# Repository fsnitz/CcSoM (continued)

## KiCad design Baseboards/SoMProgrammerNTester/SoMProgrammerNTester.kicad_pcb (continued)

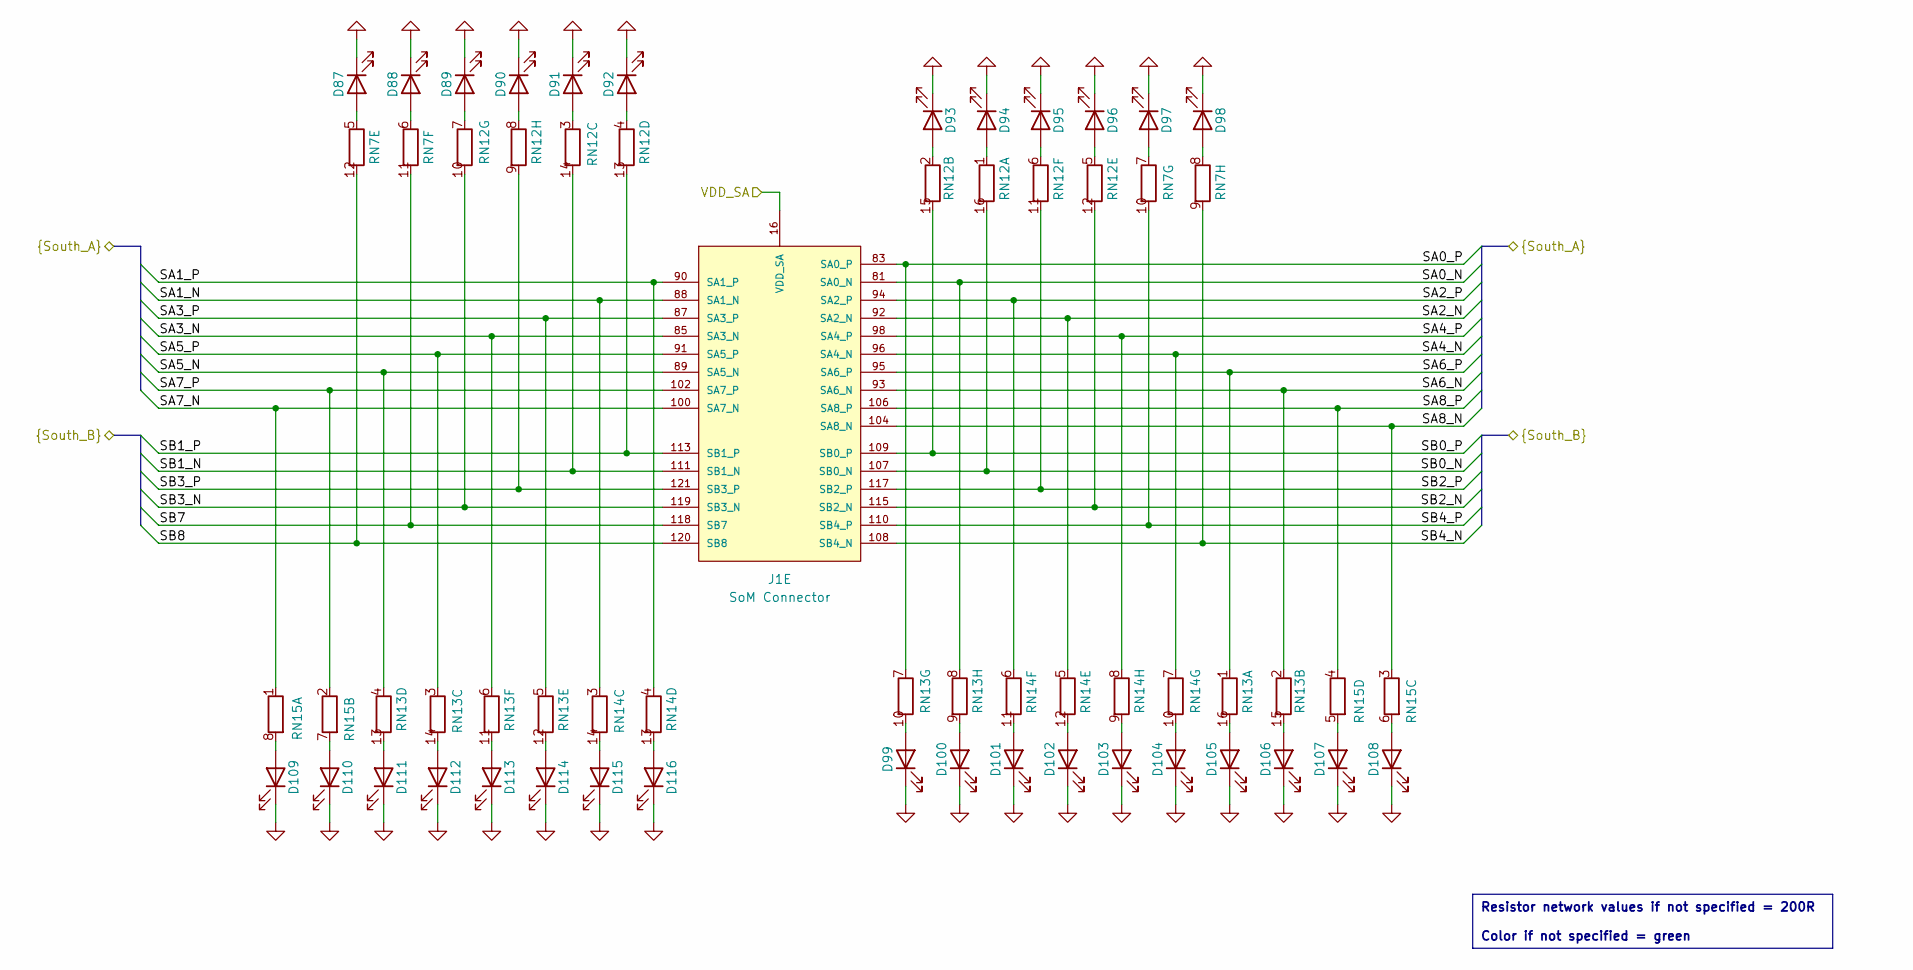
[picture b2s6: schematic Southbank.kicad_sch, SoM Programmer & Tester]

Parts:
D87, D88, D89, D90, D91, D92, D93, D94, D95, D96, D97, D98, D99, D100, D101, D102, D103, D104, D105, D106, D107, D108, D109, D110, D111, D112, D113, D114, D115, D116: Green; LED_0603_1608Metric; Mouser Part Number 710-150060VS75000
J1: SoM Connector; SoM_Connector; Mouser Part Number 571-1473005-1
RN7, RN12, RN13, RN14: 200R; R_Array_Convex_8x0602; Mouser Part Number 667-EXB-2HV201JV
RN15: 200R; R_Array_Convex_4x0603; Mouser Part Number 667-EXB-38V201JV

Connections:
/Header Interface/SA0_N: J1.81 (SA0_N), RN13.8 (R8.1); also elsewhere on the board
/Header Interface/SA0_P: J1.83 (SA0_P), RN13.7 (R7.1); also elsewhere on the board
/Header Interface/SA1_N: J1.88 (SA1_N), RN14.3 (R3.1); also elsewhere on the board
/Header Interface/SA1_P: J1.90 (SA1_P), RN14.4 (R4.1); also elsewhere on the board
/Header Interface/SA2_N: J1.92 (SA2_N), RN14.5 (R5.1); also elsewhere on the board
/Header Interface/SA2_P: J1.94 (SA2_P), RN14.6 (R6.1); also elsewhere on the board
/Header Interface/SA3_N: J1.85 (SA3_N), RN13.6 (R6.1); also elsewhere on the board
/Header Interface/SA3_P: J1.87 (SA3_P), RN13.5 (R5.1); also elsewhere on the board
/Header Interface/SA4_N: J1.96 (SA4_N), RN14.7 (R7.1); also elsewhere on the board
/Header Interface/SA4_P: J1.98 (SA4_P), RN14.8 (R8.1); also elsewhere on the board
/Header Interface/SA5_N: J1.89 (SA5_N), RN13.4 (R4.1); also elsewhere on the board
/Header Interface/SA5_P: J1.91 (SA5_P), RN13.3 (R3.1); also elsewhere on the board
/Header Interface/SA6_N: J1.93 (SA6_N), RN13.2 (R2.1); also elsewhere on the board
/Header Interface/SA6_P: J1.95 (SA6_P), RN13.1 (R1.1); also elsewhere on the board
/Header Interface/SA7_N: J1.100 (SA7_N), RN15.1 (R1.1); also elsewhere on the board
/Header Interface/SA7_P: J1.102 (SA7_P), RN15.2 (R2.1); also elsewhere on the board
/Header Interface/SA8_N: J1.104 (SA8_N), RN15.3 (R3.1); also elsewhere on the board
/Header Interface/SA8_P: J1.106 (SA8_P), RN15.4 (R4.1); also elsewhere on the board
/Header Interface/SB0_N: J1.107 (SB0_N), RN12.16 (R1.2); also elsewhere on the board
/Header Interface/SB0_P: J1.109 (SB0_P), RN12.15 (R2.2); also elsewhere on the board
/Header Interface/SB1_N: J1.111 (SB1_N), RN12.14 (R3.2); also elsewhere on the board
/Header Interface/SB1_P: J1.113 (SB1_P), RN12.13 (R4.2); also elsewhere on the board
/Header Interface/SB2_N: J1.115 (SB2_N), RN12.12 (R5.2); also elsewhere on the board
/Header Interface/SB2_P: J1.117 (SB2_P), RN12.11 (R6.2); also elsewhere on the board
/Header Interface/SB3_N: J1.119 (SB3_N), RN12.10 (R7.2); also elsewhere on the board
/Header Interface/SB3_P: J1.121 (SB3_P), RN12.9 (R8.2); also elsewhere on the board
/Header Interface/SB4_N: J1.108 (SB4_N), RN7.9 (R8.2); also elsewhere on the board
/Header Interface/SB4_P: J1.110 (SB4_P), RN7.10 (R7.2); also elsewhere on the board
/Header Interface/SB7: J1.118 (SB7), RN7.11 (R6.2); also elsewhere on the board
/Header Interface/SB8: J1.120 (SB8), RN7.12 (R5.2); also elsewhere on the board
/Header Interface/Southbank/VDD_SA: J1.16 (VDD_SA); also elsewhere on the board
GND: D87.1 (K), D88.1 (K), D89.1 (K), D90.1 (K), D91.1 (K), D92.1 (K), D93.1 (K), D94.1 (K), D95.1 (K), D96.1 (K), D97.1 (K), D98.1 (K), D99.1 (K), D100.1 (K), D101.1 (K), D102.1 (K), D103.1 (K), D104.1 (K), D105.1 (K), D106.1 (K), D107.1 (K), D108.1 (K), D109.1 (K), D110.1 (K), D111.1 (K), D112.1 (K), D113.1 (K), D114.1 (K), D115.1 (K), D116.1 (K); also elsewhere on the board
unnamed: D87.2 (A), RN7.5 (R5.1)
unnamed: D88.2 (A), RN7.6 (R6.1)
unnamed: D89.2 (A), RN12.7 (R7.1)
unnamed: D90.2 (A), RN12.8 (R8.1)
unnamed: D91.2 (A), RN12.3 (R3.1)
unnamed: D92.2 (A), RN12.4 (R4.1)
unnamed: D93.2 (A), RN12.2 (R2.1)
unnamed: D94.2 (A), RN12.1 (R1.1)
unnamed: D95.2 (A), RN12.6 (R6.1)
unnamed: D96.2 (A), RN12.5 (R5.1)
unnamed: D97.2 (A), RN7.7 (R7.1)
unnamed: D98.2 (A), RN7.8 (R8.1)
unnamed: D99.2 (A), RN13.10 (R7.2)
unnamed: D100.2 (A), RN13.9 (R8.2)
unnamed: D101.2 (A), RN14.11 (R6.2)
unnamed: D102.2 (A), RN14.12 (R5.2)
unnamed: D103.2 (A), RN14.9 (R8.2)
unnamed: D104.2 (A), RN14.10 (R7.2)
unnamed: D105.2 (A), RN13.16 (R1.2)
unnamed: D106.2 (A), RN13.15 (R2.2)
unnamed: D107.2 (A), RN15.5 (R4.2)
unnamed: D108.2 (A), RN15.6 (R3.2)
unnamed: D109.2 (A), RN15.8 (R1.2)
unnamed: D110.2 (A), RN15.7 (R2.2)
unnamed: D111.2 (A), RN13.13 (R4.2)
unnamed: D112.2 (A), RN13.14 (R3.2)
unnamed: D113.2 (A), RN13.11 (R6.2)
unnamed: D114.2 (A), RN13.12 (R5.2)
unnamed: D115.2 (A), RN14.14 (R3.2)
unnamed: D116.2 (A), RN14.13 (R4.2)

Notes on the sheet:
Resistor network values if not specified = 200R Color if not specified = green

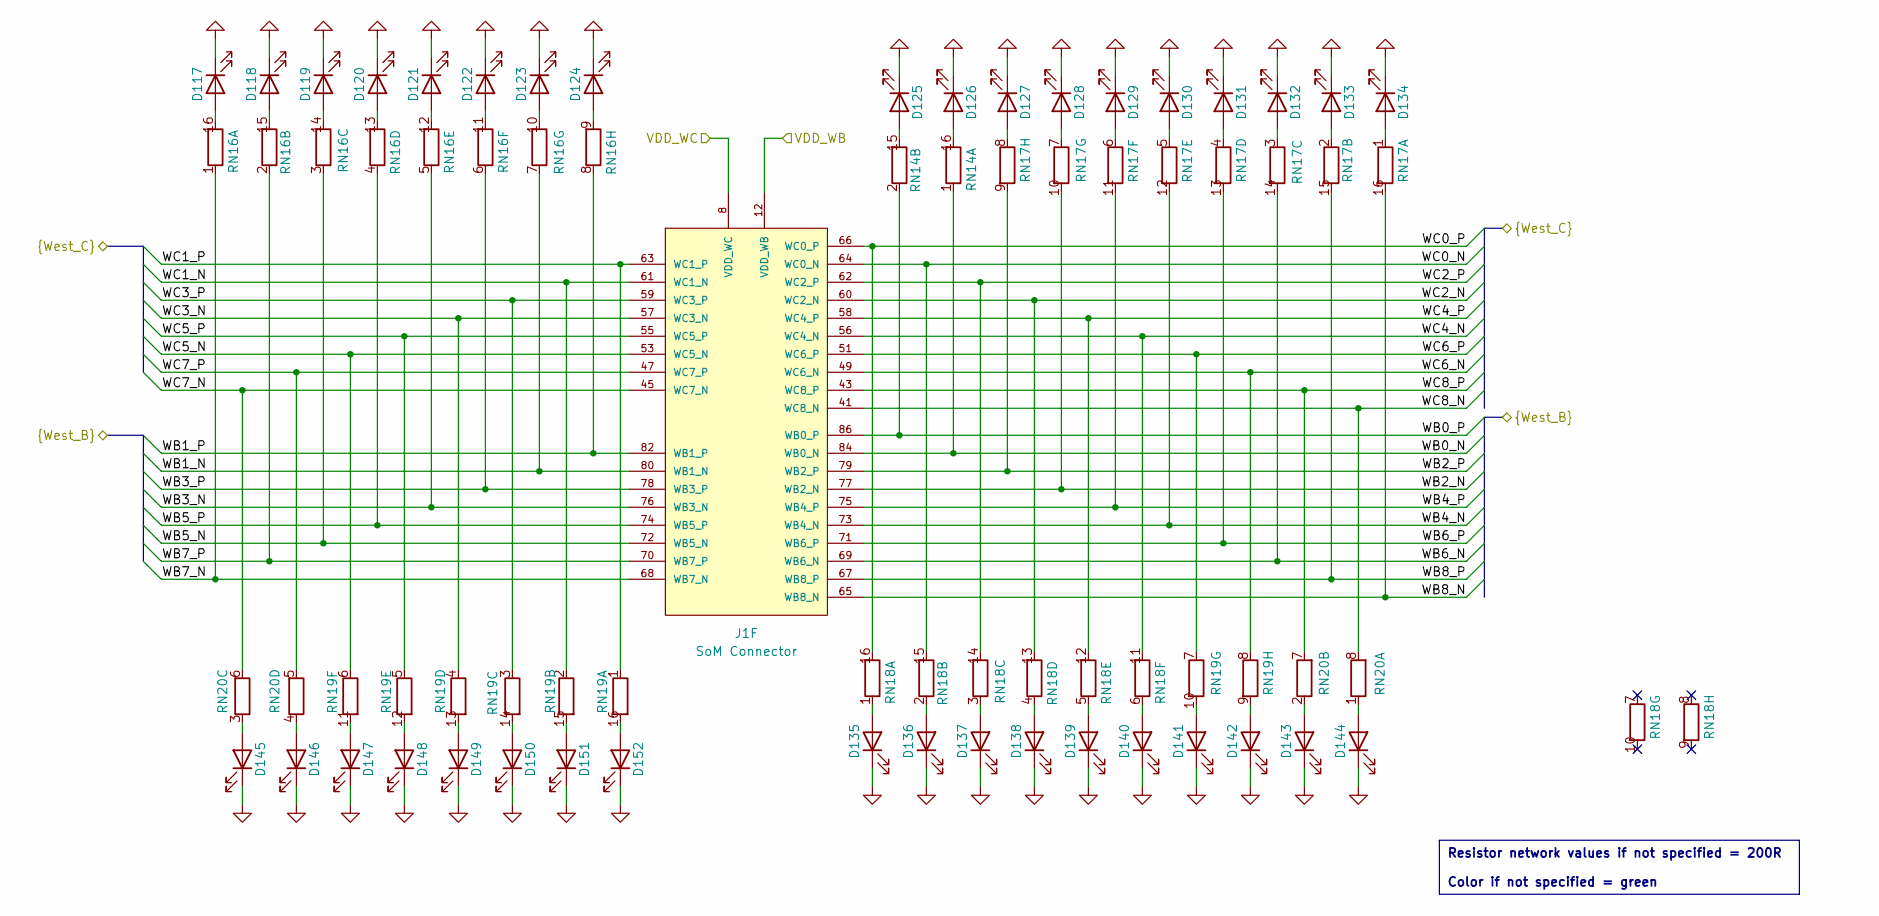
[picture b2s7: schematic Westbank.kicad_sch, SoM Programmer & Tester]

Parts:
D117, D118, D119, D120, D121, D122, D123, D124, D125, D126, D127, D128, D129, D130, D131, D132, D133, D134, D135, D136, D137, D138, D139, D140, D141, D142, D143, D144, D145, D146, D147, D148, D149, D150, D151, D152: Green; LED_0603_1608Metric; Mouser Part Number 710-150060VS75000
J1: SoM Connector; SoM_Connector; Mouser Part Number 571-1473005-1
RN14, RN16, RN17, RN18, RN19: 200R; R_Array_Convex_8x0602; Mouser Part Number 667-EXB-2HV201JV
RN20: 200R; R_Array_Convex_4x0603; Mouser Part Number 667-EXB-38V201JV

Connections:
/Header Interface/WB0_N: J1.84 (WB0_N), RN14.1 (R1.1); also elsewhere on the board
/Header Interface/WB0_P: J1.86 (WB0_P), RN14.2 (R2.1); also elsewhere on the board
/Header Interface/WB1_N: J1.80 (WB1_N), RN16.7 (R7.1); also elsewhere on the board
/Header Interface/WB1_P: J1.82 (WB1_P), RN16.8 (R8.1); also elsewhere on the board
/Header Interface/WB2_N: J1.77 (WB2_N), RN17.10 (R7.2); also elsewhere on the board
/Header Interface/WB2_P: J1.79 (WB2_P), RN17.9 (R8.2); also elsewhere on the board
/Header Interface/WB3_N: J1.76 (WB3_N), RN16.5 (R5.1); also elsewhere on the board
/Header Interface/WB3_P: J1.78 (WB3_P), RN16.6 (R6.1); also elsewhere on the board
/Header Interface/WB4_N: J1.73 (WB4_N), RN17.12 (R5.2); also elsewhere on the board
/Header Interface/WB4_P: J1.75 (WB4_P), RN17.11 (R6.2); also elsewhere on the board
/Header Interface/WB5_N: J1.72 (WB5_N), RN16.3 (R3.1); also elsewhere on the board
/Header Interface/WB5_P: J1.74 (WB5_P), RN16.4 (R4.1); also elsewhere on the board
/Header Interface/WB6_N: J1.69 (WB6_N), RN17.14 (R3.2); also elsewhere on the board
/Header Interface/WB6_P: J1.71 (WB6_P), RN17.13 (R4.2); also elsewhere on the board
/Header Interface/WB7_N: J1.68 (WB7_N), RN16.1 (R1.1); also elsewhere on the board
/Header Interface/WB7_P: J1.70 (WB7_P), RN16.2 (R2.1); also elsewhere on the board
/Header Interface/WB8_N: J1.65 (WB8_N), RN17.16 (R1.2); also elsewhere on the board
/Header Interface/WB8_P: J1.67 (WB8_P), RN17.15 (R2.2); also elsewhere on the board
/Header Interface/WC0_N: J1.64 (WC0_N), RN18.15 (R2.2); also elsewhere on the board
/Header Interface/WC0_P: J1.66 (WC0_P), RN18.16 (R1.2); also elsewhere on the board
/Header Interface/WC1_N: J1.61 (WC1_N), RN19.2 (R2.1); also elsewhere on the board
/Header Interface/WC1_P: J1.63 (WC1_P), RN19.1 (R1.1); also elsewhere on the board
/Header Interface/WC2_N: J1.60 (WC2_N), RN18.13 (R4.2); also elsewhere on the board
/Header Interface/WC2_P: J1.62 (WC2_P), RN18.14 (R3.2); also elsewhere on the board
/Header Interface/WC3_N: J1.57 (WC3_N), RN19.4 (R4.1); also elsewhere on the board
/Header Interface/WC3_P: J1.59 (WC3_P), RN19.3 (R3.1); also elsewhere on the board
/Header Interface/WC4_N: J1.56 (WC4_N), RN18.11 (R6.2); also elsewhere on the board
/Header Interface/WC4_P: J1.58 (WC4_P), RN18.12 (R5.2); also elsewhere on the board
/Header Interface/WC5_N: J1.53 (WC5_N), RN19.6 (R6.1); also elsewhere on the board
/Header Interface/WC5_P: J1.55 (WC5_P), RN19.5 (R5.1); also elsewhere on the board
/Header Interface/WC6_N: J1.49 (WC6_N), RN19.8 (R8.1); also elsewhere on the board
/Header Interface/WC6_P: J1.51 (WC6_P), RN19.7 (R7.1); also elsewhere on the board
/Header Interface/WC7_N: J1.45 (WC7_N), RN20.6 (R3.2); also elsewhere on the board
/Header Interface/WC7_P: J1.47 (WC7_P), RN20.5 (R4.2); also elsewhere on the board
/Header Interface/WC8_N: J1.41 (WC8_N), RN20.8 (R1.2); also elsewhere on the board
/Header Interface/WC8_P: J1.43 (WC8_P), RN20.7 (R2.2); also elsewhere on the board
/Header Interface/Westbank/VDD_WB: J1.12 (VDD_WB); also elsewhere on the board
/Header Interface/Westbank/VDD_WC: J1.8 (VDD_WC); also elsewhere on the board
GND: D117.1 (K), D118.1 (K), D119.1 (K), D120.1 (K), D121.1 (K), D122.1 (K), D123.1 (K), D124.1 (K), D125.1 (K), D126.1 (K), D127.1 (K), D128.1 (K), D129.1 (K), D130.1 (K), D131.1 (K), D132.1 (K), D133.1 (K), D134.1 (K), D135.1 (K), D136.1 (K), D137.1 (K), D138.1 (K), D139.1 (K), D140.1 (K), D141.1 (K), D142.1 (K), D143.1 (K), D144.1 (K), D145.1 (K), D146.1 (K), D147.1 (K), D148.1 (K), D149.1 (K), D150.1 (K), D151.1 (K), D152.1 (K); also elsewhere on the board
unnamed: D117.2 (A), RN16.16 (R1.2)
unnamed: D118.2 (A), RN16.15 (R2.2)
unnamed: D119.2 (A), RN16.14 (R3.2)
unnamed: D120.2 (A), RN16.13 (R4.2)
unnamed: D121.2 (A), RN16.12 (R5.2)
unnamed: D122.2 (A), RN16.11 (R6.2)
unnamed: D123.2 (A), RN16.10 (R7.2)
unnamed: D124.2 (A), RN16.9 (R8.2)
unnamed: D125.2 (A), RN14.15 (R2.2)
unnamed: D126.2 (A), RN14.16 (R1.2)
unnamed: D127.2 (A), RN17.8 (R8.1)
unnamed: D128.2 (A), RN17.7 (R7.1)
unnamed: D129.2 (A), RN17.6 (R6.1)
unnamed: D130.2 (A), RN17.5 (R5.1)
unnamed: D131.2 (A), RN17.4 (R4.1)
unnamed: D132.2 (A), RN17.3 (R3.1)
unnamed: D133.2 (A), RN17.2 (R2.1)
unnamed: D134.2 (A), RN17.1 (R1.1)
unnamed: D135.2 (A), RN18.1 (R1.1)
unnamed: D136.2 (A), RN18.2 (R2.1)
unnamed: D137.2 (A), RN18.3 (R3.1)
unnamed: D138.2 (A), RN18.4 (R4.1)
unnamed: D139.2 (A), RN18.5 (R5.1)
unnamed: D140.2 (A), RN18.6 (R6.1)
unnamed: D141.2 (A), RN19.10 (R7.2)
unnamed: D142.2 (A), RN19.9 (R8.2)
unnamed: D143.2 (A), RN20.2 (R2.1)
unnamed: D144.2 (A), RN20.1 (R1.1)
unnamed: D145.2 (A), RN20.3 (R3.1)
unnamed: D146.2 (A), RN20.4 (R4.1)
unnamed: D147.2 (A), RN19.11 (R6.2)
unnamed: D148.2 (A), RN19.12 (R5.2)
unnamed: D149.2 (A), RN19.13 (R4.2)
unnamed: D150.2 (A), RN19.14 (R3.2)
unnamed: D151.2 (A), RN19.15 (R2.2)
unnamed: D152.2 (A), RN19.16 (R1.2)

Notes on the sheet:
Resistor network values if not specified = 200R Color if not specified = green

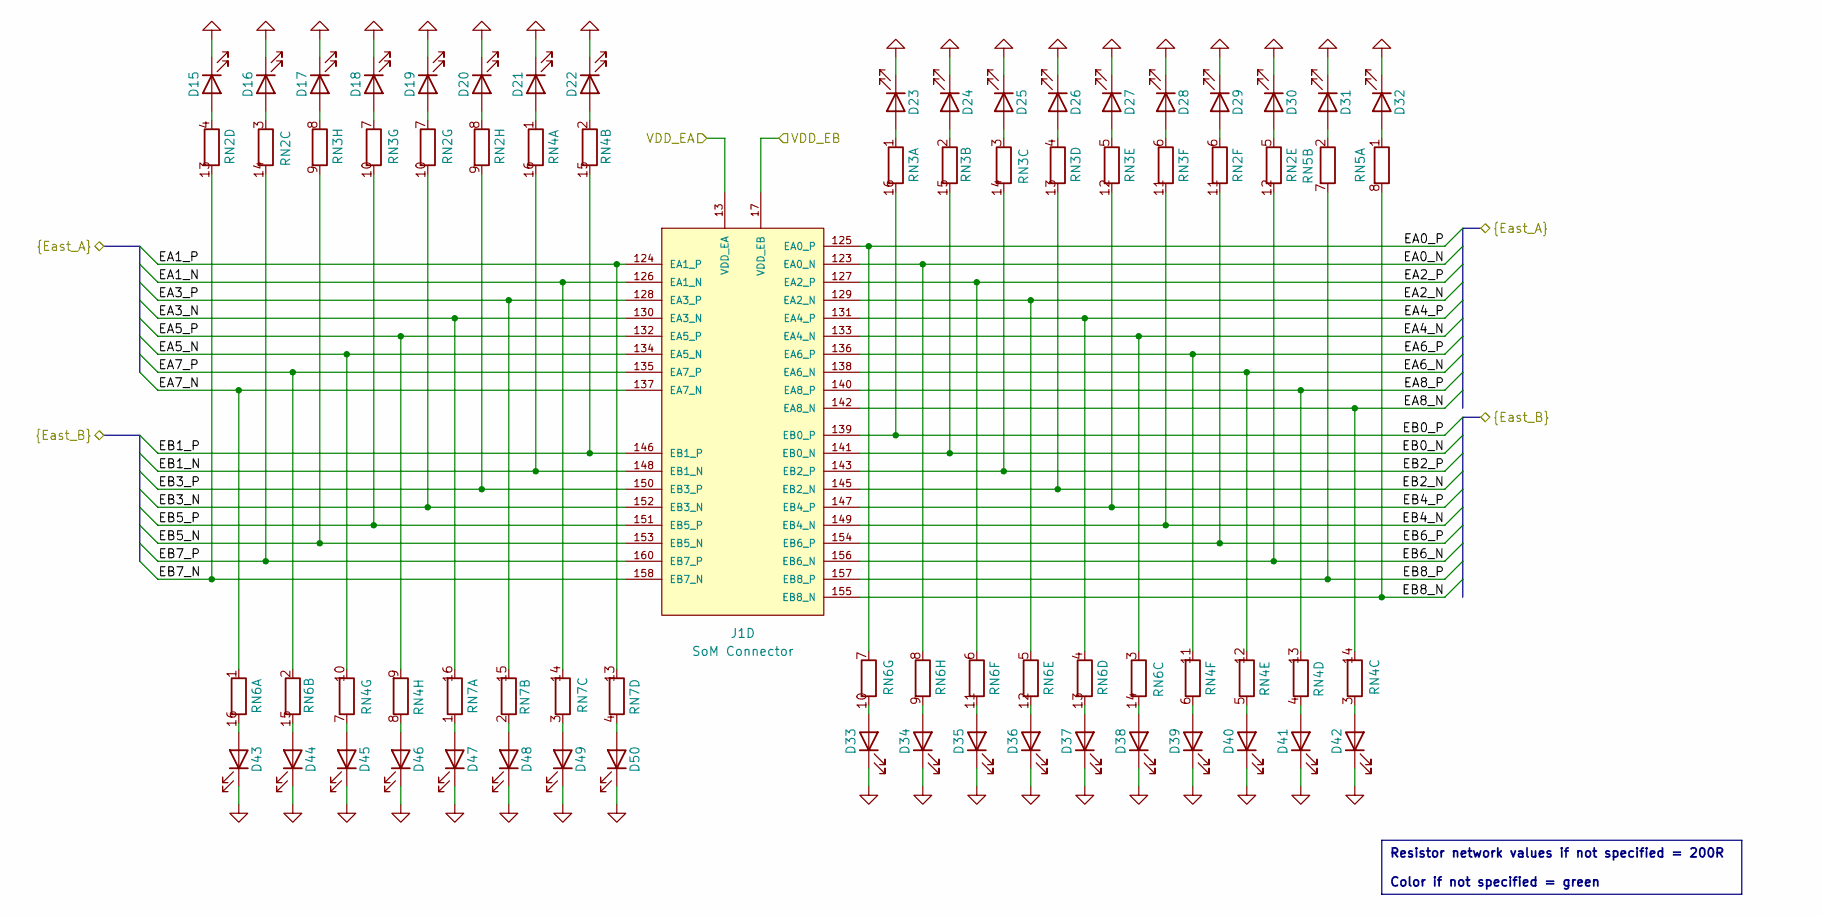
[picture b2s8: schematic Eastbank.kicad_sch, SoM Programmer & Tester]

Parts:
D15, D16, D17, D18, D19, D20, D21, D22, D23, D24, D25, D26, D27, D28, D29, D30, D31, D32, D33, D34, D35, D36, D37, D38, D39, D40, D41, D42, D43, D44, D45, D46, D47, D48, D49, D50: Green; LED_0603_1608Metric; Mouser Part Number 710-150060VS75000
J1: SoM Connector; SoM_Connector; Mouser Part Number 571-1473005-1
RN2, RN3, RN4, RN6, RN7: 200R; R_Array_Convex_8x0602; Mouser Part Number 667-EXB-2HV201JV
RN5: 200R; R_Array_Convex_4x0603; Mouser Part Number 667-EXB-38V201JV

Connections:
/Header Interface/EA0_N: J1.123 (EA0_N), RN6.8 (R8.1); also elsewhere on the board
/Header Interface/EA0_P: J1.125 (EA0_P), RN6.7 (R7.1); also elsewhere on the board
/Header Interface/EA1_N: J1.126 (EA1_N), RN7.14 (R3.2); also elsewhere on the board
/Header Interface/EA1_P: J1.124 (EA1_P), RN7.13 (R4.2); also elsewhere on the board
/Header Interface/EA2_N: J1.129 (EA2_N), RN6.5 (R5.1); also elsewhere on the board
/Header Interface/EA2_P: J1.127 (EA2_P), RN6.6 (R6.1); also elsewhere on the board
/Header Interface/EA3_N: J1.130 (EA3_N), RN7.16 (R1.2); also elsewhere on the board
/Header Interface/EA3_P: J1.128 (EA3_P), RN7.15 (R2.2); also elsewhere on the board
/Header Interface/EA4_N: J1.133 (EA4_N), RN6.3 (R3.1); also elsewhere on the board
/Header Interface/EA4_P: J1.131 (EA4_P), RN6.4 (R4.1); also elsewhere on the board
/Header Interface/EA5_N: J1.134 (EA5_N), RN4.10 (R7.2); also elsewhere on the board
/Header Interface/EA5_P: J1.132 (EA5_P), RN4.9 (R8.2); also elsewhere on the board
/Header Interface/EA6_N: J1.138 (EA6_N), RN4.12 (R5.2); also elsewhere on the board
/Header Interface/EA6_P: J1.136 (EA6_P), RN4.11 (R6.2); also elsewhere on the board
/Header Interface/EA7_N: J1.137 (EA7_N), RN6.1 (R1.1); also elsewhere on the board
/Header Interface/EA7_P: J1.135 (EA7_P), RN6.2 (R2.1); also elsewhere on the board
/Header Interface/EA8_N: J1.142 (EA8_N), RN4.14 (R3.2); also elsewhere on the board
/Header Interface/EA8_P: J1.140 (EA8_P), RN4.13 (R4.2); also elsewhere on the board
/Header Interface/EB0_N: J1.141 (EB0_N), RN3.15 (R2.2); also elsewhere on the board
/Header Interface/EB0_P: J1.139 (EB0_P), RN3.16 (R1.2); also elsewhere on the board
/Header Interface/EB1_N: J1.148 (EB1_N), RN4.16 (R1.2); also elsewhere on the board
/Header Interface/EB1_P: J1.146 (EB1_P), RN4.15 (R2.2); also elsewhere on the board
/Header Interface/EB2_N: J1.145 (EB2_N), RN3.13 (R4.2); also elsewhere on the board
/Header Interface/EB2_P: J1.143 (EB2_P), RN3.14 (R3.2); also elsewhere on the board
/Header Interface/EB3_N: J1.152 (EB3_N), RN2.10 (R7.2); also elsewhere on the board
/Header Interface/EB3_P: J1.150 (EB3_P), RN2.9 (R8.2); also elsewhere on the board
/Header Interface/EB4_N: J1.149 (EB4_N), RN3.11 (R6.2); also elsewhere on the board
/Header Interface/EB4_P: J1.147 (EB4_P), RN3.12 (R5.2); also elsewhere on the board
/Header Interface/EB5_N: J1.153 (EB5_N), RN3.9 (R8.2); also elsewhere on the board
/Header Interface/EB5_P: J1.151 (EB5_P), RN3.10 (R7.2); also elsewhere on the board
/Header Interface/EB6_N: J1.156 (EB6_N), RN2.12 (R5.2); also elsewhere on the board
/Header Interface/EB6_P: J1.154 (EB6_P), RN2.11 (R6.2); also elsewhere on the board
/Header Interface/EB7_N: J1.158 (EB7_N), RN2.13 (R4.2); also elsewhere on the board
/Header Interface/EB7_P: J1.160 (EB7_P), RN2.14 (R3.2); also elsewhere on the board
/Header Interface/EB8_N: J1.155 (EB8_N), RN5.8 (R1.2); also elsewhere on the board
/Header Interface/EB8_P: J1.157 (EB8_P), RN5.7 (R2.2); also elsewhere on the board
/Header Interface/Eastbank/VDD_EA: J1.13 (VDD_EA); also elsewhere on the board
/Header Interface/Eastbank/VDD_EB: J1.17 (VDD_EB); also elsewhere on the board
GND: D15.1 (K), D16.1 (K), D17.1 (K), D18.1 (K), D19.1 (K), D20.1 (K), D21.1 (K), D22.1 (K), D23.1 (K), D24.1 (K), D25.1 (K), D26.1 (K), D27.1 (K), D28.1 (K), D29.1 (K), D30.1 (K), D31.1 (K), D32.1 (K), D33.1 (K), D34.1 (K), D35.1 (K), D36.1 (K), D37.1 (K), D38.1 (K), D39.1 (K), D40.1 (K), D41.1 (K), D42.1 (K), D43.1 (K), D44.1 (K), D45.1 (K), D46.1 (K), D47.1 (K), D48.1 (K), D49.1 (K), D50.1 (K); also elsewhere on the board
unnamed: D15.2 (A), RN2.4 (R4.1)
unnamed: D16.2 (A), RN2.3 (R3.1)
unnamed: D17.2 (A), RN3.8 (R8.1)
unnamed: D18.2 (A), RN3.7 (R7.1)
unnamed: D19.2 (A), RN2.7 (R7.1)
unnamed: D20.2 (A), RN2.8 (R8.1)
unnamed: D21.2 (A), RN4.1 (R1.1)
unnamed: D22.2 (A), RN4.2 (R2.1)
unnamed: D23.2 (A), RN3.1 (R1.1)
unnamed: D24.2 (A), RN3.2 (R2.1)
unnamed: D25.2 (A), RN3.3 (R3.1)
unnamed: D26.2 (A), RN3.4 (R4.1)
unnamed: D27.2 (A), RN3.5 (R5.1)
unnamed: D28.2 (A), RN3.6 (R6.1)
unnamed: D29.2 (A), RN2.6 (R6.1)
unnamed: D30.2 (A), RN2.5 (R5.1)
unnamed: D31.2 (A), RN5.2 (R2.1)
unnamed: D32.2 (A), RN5.1 (R1.1)
unnamed: D33.2 (A), RN6.10 (R7.2)
unnamed: D34.2 (A), RN6.9 (R8.2)
unnamed: D35.2 (A), RN6.11 (R6.2)
unnamed: D36.2 (A), RN6.12 (R5.2)
unnamed: D37.2 (A), RN6.13 (R4.2)
unnamed: D38.2 (A), RN6.14 (R3.2)
unnamed: D39.2 (A), RN4.6 (R6.1)
unnamed: D40.2 (A), RN4.5 (R5.1)
unnamed: D41.2 (A), RN4.4 (R4.1)
unnamed: D42.2 (A), RN4.3 (R3.1)
unnamed: D43.2 (A), RN6.16 (R1.2)
unnamed: D44.2 (A), RN6.15 (R2.2)
unnamed: D45.2 (A), RN4.7 (R7.1)
unnamed: D46.2 (A), RN4.8 (R8.1)
unnamed: D47.2 (A), RN7.1 (R1.1)
unnamed: D48.2 (A), RN7.2 (R2.1)
unnamed: D49.2 (A), RN7.3 (R3.1)
unnamed: D50.2 (A), RN7.4 (R4.1)

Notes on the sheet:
Resistor network values if not specified = 200R Color if not specified = green

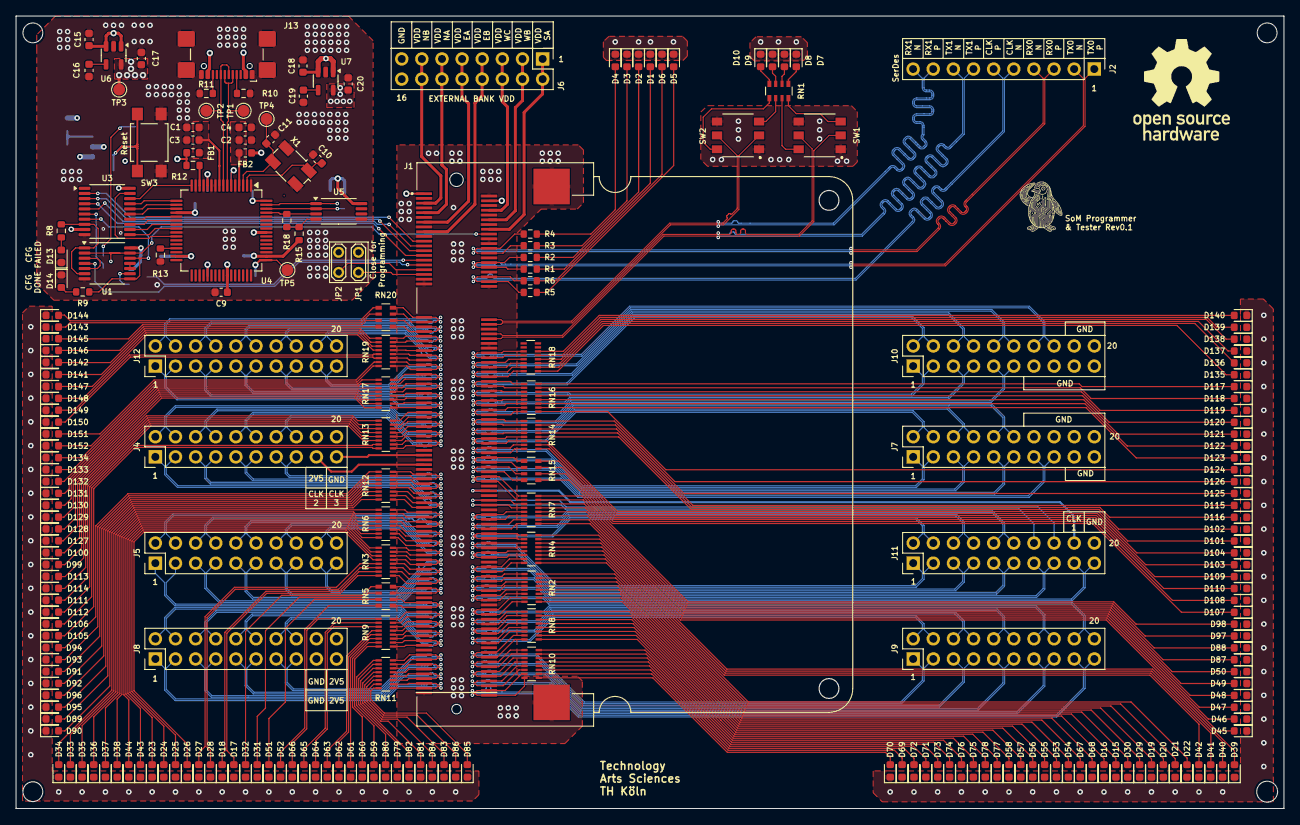
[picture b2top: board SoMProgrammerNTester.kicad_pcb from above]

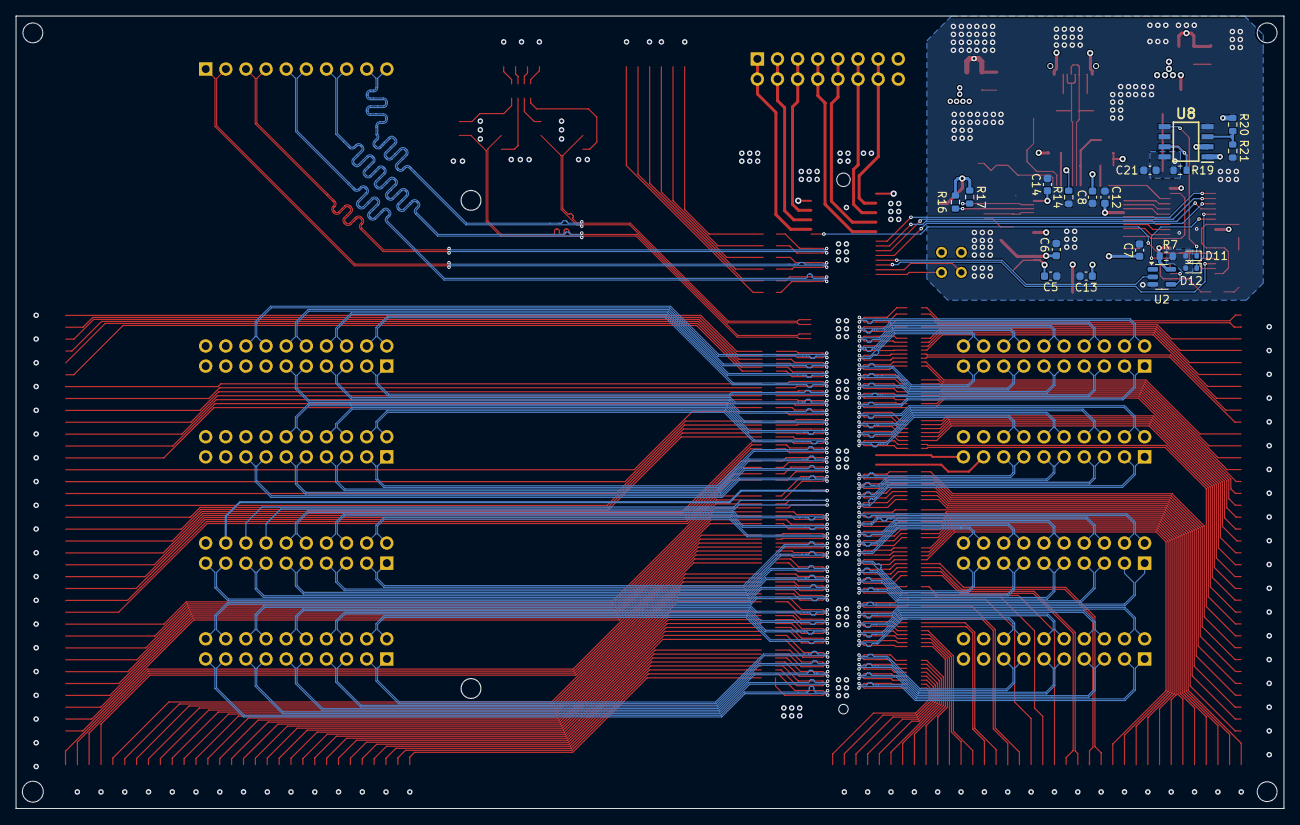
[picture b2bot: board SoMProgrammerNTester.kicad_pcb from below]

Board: 4 copper layers, 160.0 x 100.0 mm, 249 parts (19 on the bottom side), 361 nets.

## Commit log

2024-12-20 Release commit
2024-12-20 Update README.md
    Added initial version of the readme
2024-12-20 Readme shifted to front page
2025-02-27 Add Firmware for SoMProgrammerNTester
2026-02-22 Created Version with 0402 components
2026-02-22 Revise 0402 footprint version availability details
    Updated information about the 0402 footprint version availability.
2026-02-23 Add Part Number to SoM-BOM
